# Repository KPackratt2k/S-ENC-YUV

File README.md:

# S-ENC-YUV
A YPbPr mod kit for the first generation SNES and Super Famicom consoles utilizing the BA6592F and S-ENC (a.k.a. BA6594F) video encoder chips.

**NOTICE:** This mod has been abandoned for a variety of reasons. Due to the video encoder's color difference pins outputting in the YIQ (for NTSC) or YUV (for PAL) colorspace, there are inaccurate colors when using this mod. In addition, I've experienced noise in the Luma channel on the console I've tested this with and have been unable to elimiate it entirely. If you're looking to use an SNES console on an SDTV or PVM with YPbPr inputs, I would recommend using an RGB SCART cable and an external RGB-to-YPbPr transcoder instead. If you choose to perform this mod to your console, understand its drawbacks and perform at your own risk.

**IMPORTANT:** This mod is compatible with early SNES and Super Famicom console revisions (serial number beginning with UN272 or less) only. Later SNES and Super Famicom consoles which utilize the S-RGB encoder lack the Pb and Pr outputs necessary for this mod, therefore this mod will not work on later consoles.

Compatible revisions:
- SHVC-CPU-01
- SNS-CPU-GPM-01
- SNS-CPU-GPM-02
- SNSP-CPU-01
- SNSP-CPU-02

The SNES outputs at a 15KHz 240p resolution, which most modern HDTVs will not accept over Component YPbPr (even if it can accept it over Composite). Please refer to [this webpage](https://www.hdretrovision.com/240p) for a list of TVs that have been tested as well as instructions on how to determine if your set can accept a 240p input in the event you can't find your TV in the compatibility list. If your TV cannot accept 240p over Component, then you must use a dedicated video scaler (e.g. RetroTink 2X, RetroTink 5X, OSSC, Framemeister, or GBS Control) to upscale the 240p signal. Users of CRT SDTVs, PVMs, or BVMs may disregard this message.

------------

## Introduction

As more gamers discover the benefits that RGB has to offer over the bog-standard Composite, they are often faced with the confusion surrounding the available options for taking advantage of this feature. The first instinct would be to head on over to eBay or Amazon and buy the cheapest SCART cables they can find, only to be disappointed by the audio buzzing and interference caused by cheap unshielded cables. Higher quality options like HD Retrovision Component cables or SCART cables from Insurrection Industries, Retro Access, or Retro Gaming Cables tend to fluctuate in stock as more people buy them. This mod enables early SNES or Super Famicom console revisions to output YPbPr Component Video using a cheap readily available 3.5mm TRRS to 3x RCA cable in conjunction with the standard Nintendo Composite AV cables for sound.

------------

## Variations

There are multiple variations of the mod board to choose from based on the two different methods tested. The one to choose will vary on a variety of factors (such as your video encoder chip, console revision, or even your TV/Scaler's way of processing the image). Type A uses a transistor setup similar to the original AV output circuit of the SNES and is best suited for the BA6592F encoder (common on most SHVC-CPU-01 consoles), while Type B uses basic passive components and is suited best for the S-ENC encoder (common on all other compatible revisions). If you're not sure which one to use, order the advanced full-size board and test it with different configurations to see which one works best for you.

OSHPark links:
- [Advanced](https://oshpark.com/shared_projects/vhEn3k7J)
- [Mini Type-A](https://oshpark.com/shared_projects/W2nKIRFb)
- [Mini Type-B](https://oshpark.com/shared_projects/YYqaIlj8)
- [Multi-Out Board for easy installation](https://oshpark.com/shared_projects/abuhMZIt)

It is recommended to order the small Multi-Out board with a 0.8 mm thickness.

-----------

## Output Cable

It is recommended to use an XBOX 360 E Composite AV cable (easy to find for cheap) in the following configuration:
- **Yellow**: Component Y
- **White**: Component Pb
- **Red**: Component Pr

When using the wiring configuration mentioned in the mod instructions, the cable will work as intended.

I've decided against using RCA jacks for this mod because the SHVC-CPU-01 revision does not have enough room to place them on the back panel as most of the space there is taken up by the sound module.

This cable will not provide audio. You must use your old Composite AV cables to provide the audio from the console.

-----------

## Board Assembly

Refer to the Bill of Materials (BOM) documents for each board depending on the one you'll be using. Populate the components accordingly to the correct locations and solder them into place. In addition to the parts listed in the corresponding BOM documents, you will need:
- Black, Red, Yellow, Green, and Blue colored wires (I recommend 28 AWG rainbow ribbon cable for this)
- Solid core wire or leads cut from a component
- Kapton tape or electrical tape
- Double-sided tape or adhesive pads
- A Game-bit screwdriver (for opening the console)
- A Philips screwdriver (for removing the screws that hold the motherboard in place)
- Heat shrink tubes
- Soldering iron
- Side cutters
- A drill with 2mm (5/16") and 6mm (1/4") drill bits
- Q-Tip (for cleaning any residing flux)
- Isopropyl alcohol (for cleaning any residing flux)

### Advanced Board Configurations

#### Type A:
- Leave R3, R4, RV1, and RV2 unpopulated.
- Jumper R3 and R4 with solid core wire or legs from a spare component.

#### Type B:
- Leave R1, R2, D1, D2, Q1, and Q2 unpopulated.
- Jumper the D1 anode pad to the Q1 emitter pad.
- Jumper the D2 anode pad to the Q2 emitter pad.

#### Type C (WIP):
- Assemble the board in the Type B configuration, wire the board to the console, test it, and adjust the pots until the image looks correct to you.
- After adjustments are made, measure the resistance on VR1 from the negative leg of C1 to the Pb output pad, and get the closest matching resistor. Make note of the resistance so you don't mistake one resistor for another.
- Measure VR2 resistance from the negative leg of C2 to the Pr output pad, and get the closest matching resistor. Make note of its resistance.
- Remove VR1 and VR2, and install the matching resistors for Pb into R3, and the resistor for Pr into R4.

------------

## Installation

WIP: Images to be added soon and instructions will improve gradually once I have the time to finish it.

Completely disassemble your SNES or Super Famicom console and inspect the video encoder chip to determine which configuration is suitable for your console. If yours is a BA6592F encoder, the Type-A configuration should provide the best results. If it's an S-ENC or a BA6594F, then the Type-B configuration should be sufficient.

Once you have decided which configuration to use based on your video encoder type, assemble the S-ENC mod board using the BOM (Bill of Materials) and the photos above as reference.

On the back of the console motherboard, solder the Multi-Out board onto the console's AV Multi-Out connector. Make sure you don't accidentally bridge any connections in the process. Use flux if you have any available. Gently remove residing flux with a Q-Tip and isopropyl alcohol when finished.

Solder the Yellow wire to the 5V pad (optional for Types B and C), the Green wire to the Y pad, and the Black wire to the GND pad.

Reinstall the bottom shield onto the SNES motherboard, and take care routing the wires from the Multi-Out board when doing so. Avoid routing the wires close to the screw posts as doing so may cause them to get pinched and short out as a result.

Turn the console motherboard onto the front, solder the red wire onto pin 1 of the video encoder chip (the bottom-left corner pin marked by the dot) and the blue wire onto pin 24 (the top-left corner pin). On some motherboard revisions, the numbers of the pins may be labeled, which makes it easier to tell where your wires need to go.

Reinstall the RF modulator shield onto place, reinsert the screws that hold it in place, and apply electrical or kapton tape on the side above the RF modulator/jack panel.

Apply Kapton tape onto the back of the mod board, then apply the double-sided tape/adhesive pad onto the same side.

Be sure to remove the backing on the double-sided tape once applied to the board.

Stick the mod board on top of the RF shield as close to the side facing the jack panel as possible, with the output pads facing left and the input pads facing right.

Place the wires onto the corresponding input pads and cut them to size so there's as little slack as possible.

**Color Guide:**
- Black: Ground
- Yellow: 5V (Not needed for Type B/C)
- Red: Pr
- Blue: Pb
- Green: Y

Once the wires are cut to size, strip them, then tin both the wire ends and the pads on the board. Solder the wires onto their corresponding pads.

Before drilling the hole for the 3.5mm jack, apply painter's tape on the right-side of the back of the shell, take the nut off the jack, place it on the bottom-right corner of the back of the shell (next to the power jack) with the outside of the nut on the edges of the corner, then use a pencil to draw the hole inside the nut on the tape. Once you have done this, use a ruler to draw lines in the middle of the hole to aid with drilling the pilot hole for the jack.

Use a small drill bit (5/16") to drill a hole on the right-side of the bottom shell where the 3.5mm jack will be mounted. Once the small hole is drilled, use an M7x0.75 (6mm or 1/4") drill bit to enlarge the hole. Take your time when drilling the holes and be careful not to drill too fast as the plastic can be brittle depending on how well the console has been taken care of during its lifetime. Test fit the jack and enlarge the hole slightly more if necessary.

Solder wires onto the jack on the following pins:
1. Green (Sleeve)
2. Blue (Tip)
3. Red (Ring 1)
4. Black (Ring 2)

Refer to the [SJ1-43502PM Datasheet](https://www.cuidevices.com/product/resource/sj1-43502pm.pdf) for pin locations.

Once you have the wires soldered onto the jack, it would be a good idea to add heat shrink tubes onto them to reduce stress on the wires and prevent any shorts.

Install the 3.5mm jack and the SNES motherboard in the bottom shell, run the wires from the jack onto the output pads on the mod board, cut the wires to size, strip the ends of the wires, tin both the mod board pads and the wires, and solder the wires onto the corresponding pads.

Once you have the board wired up, it may be a good idea to test the console to see if the mod works. If using the Type B configuration, adjust the potentiometers until the colors look correct.

If everything is working the way it should, you can reassemble the console and enjoy.

------------

## Credits

- Nicolas Livaditis
- thesteve
- Duo_R
- Michael Moffitt
- The Console5 Wiki
- The NESDev Forum
- The PC Engine-FX Forum

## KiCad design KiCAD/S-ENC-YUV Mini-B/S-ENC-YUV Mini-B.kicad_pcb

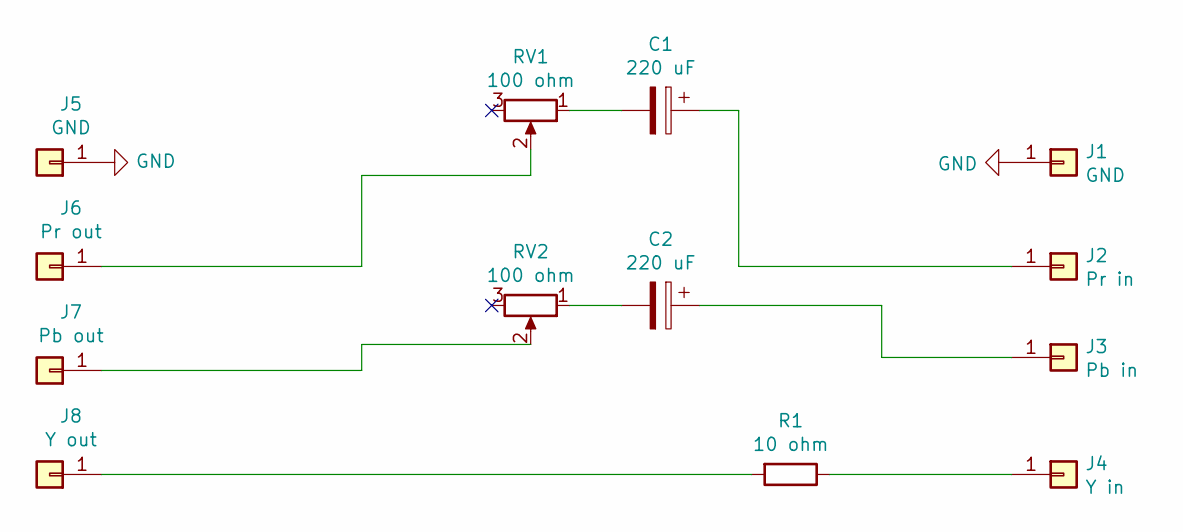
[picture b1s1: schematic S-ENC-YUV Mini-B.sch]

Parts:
C1, C2: 220 uF; CP_Radial_D6.3mm_P2.50mm
J1, J5: GND; SolderWirePad_1x01_SMD_5x10mm
J2: Pr in; SolderWirePad_1x01_SMD_5x10mm
J3: Pb in; SolderWirePad_1x01_SMD_5x10mm
J4: Y in; SolderWirePad_1x01_SMD_5x10mm
J6: Pr out; SolderWirePad_1x01_SMD_5x10mm
J7: Pb out; SolderWirePad_1x01_SMD_5x10mm
J8: Y out; SolderWirePad_1x01_SMD_5x10mm
R1: 10 ohm; R_Axial_DIN0207_L6.3mm_D2.5mm_P7.62mm_Horizontal
RV1, RV2: 100 ohm; Potentiometer_Bourns_3386P_Vertical

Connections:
GND: J1.1, J5.1
unnamed: C1.1, J2.1
unnamed: C1.2, RV1.1
unnamed: C2.1, J3.1
unnamed: C2.2, RV2.1
unnamed: J4.1, R1.1
unnamed: J6.1, RV1.2
unnamed: J7.1, RV2.2
unnamed: J8.1, R1.2

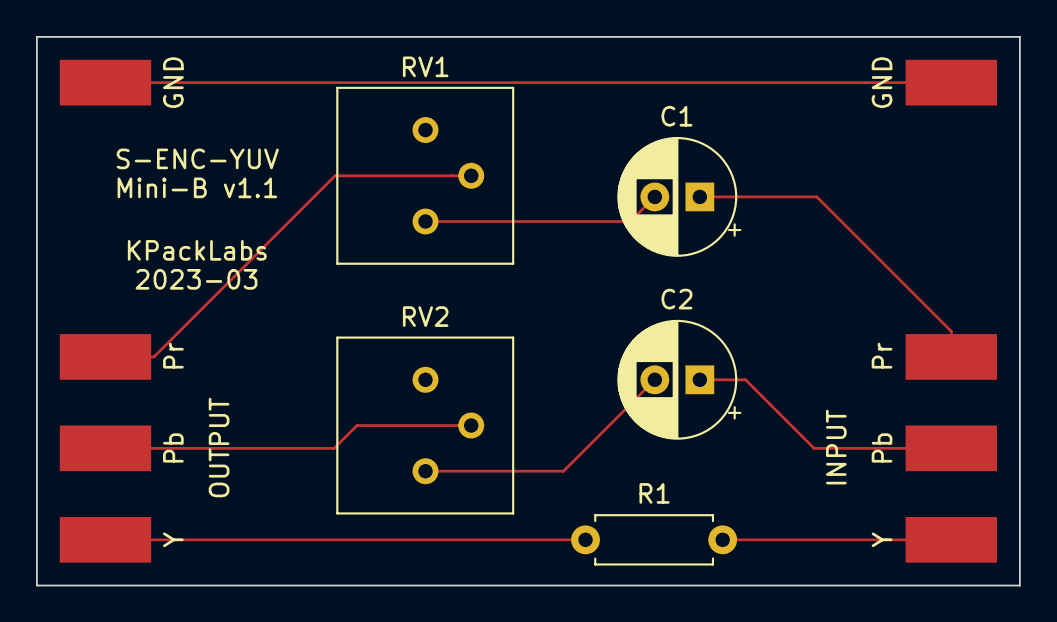
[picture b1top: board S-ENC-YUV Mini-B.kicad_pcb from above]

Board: 2 copper layers, 54.6 x 30.5 mm, 13 parts (0 on the bottom side), 9 nets.

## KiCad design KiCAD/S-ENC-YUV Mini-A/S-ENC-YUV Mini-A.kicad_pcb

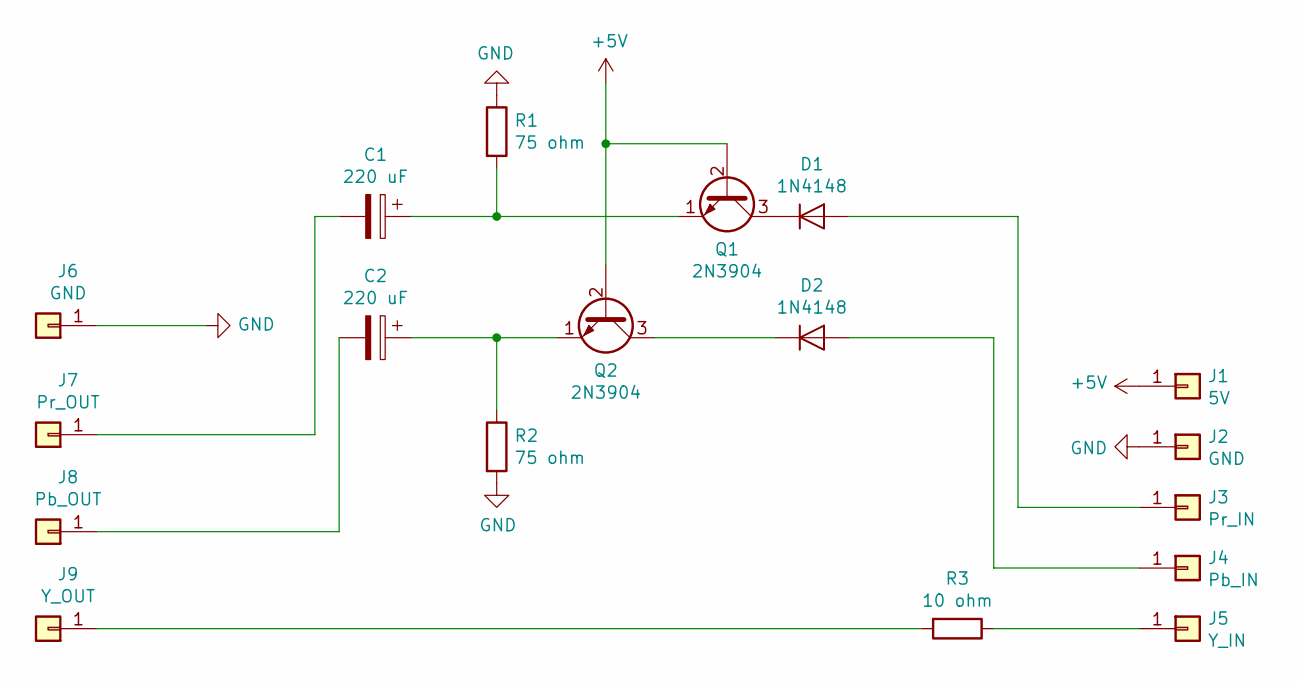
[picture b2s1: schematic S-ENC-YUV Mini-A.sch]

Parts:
C1, C2: 220 uF; CP_Radial_D6.3mm_P2.50mm
D1, D2: 1N4148; D_DO-35_SOD27_P7.62mm_Horizontal
J1: 5V; SolderWirePad_1x01_SMD_5x10mm
J2, J6: GND; SolderWirePad_1x01_SMD_5x10mm
J3: Pr_IN; SolderWirePad_1x01_SMD_5x10mm
J4: Pb_IN; SolderWirePad_1x01_SMD_5x10mm
J5: Y_IN; SolderWirePad_1x01_SMD_5x10mm
J7: Pr_OUT; SolderWirePad_1x01_SMD_5x10mm
J8: Pb_OUT; SolderWirePad_1x01_SMD_5x10mm
J9: Y_OUT; SolderWirePad_1x01_SMD_5x10mm
Q1, Q2: 2N3904; TO-92_Inline
R1, R2: 75 ohm; R_Axial_DIN0207_L6.3mm_D2.5mm_P7.62mm_Horizontal
R3: 10 ohm; R_Axial_DIN0207_L6.3mm_D2.5mm_P7.62mm_Horizontal

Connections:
+5V: J1.1, Q1.2 (B), Q2.2 (B)
GND: J2.1, J6.1, R1.1, R2.2
unnamed: C1.1, Q1.1 (E), R1.2
unnamed: C1.2, J7.1
unnamed: C2.1, Q2.1 (E), R2.1
unnamed: C2.2, J8.1
unnamed: D1.1 (K), Q1.3 (C)
unnamed: D1.2 (A), J3.1
unnamed: D2.1 (K), Q2.3 (C)
unnamed: D2.2 (A), J4.1
unnamed: J5.1, R3.1
unnamed: J9.1, R3.2

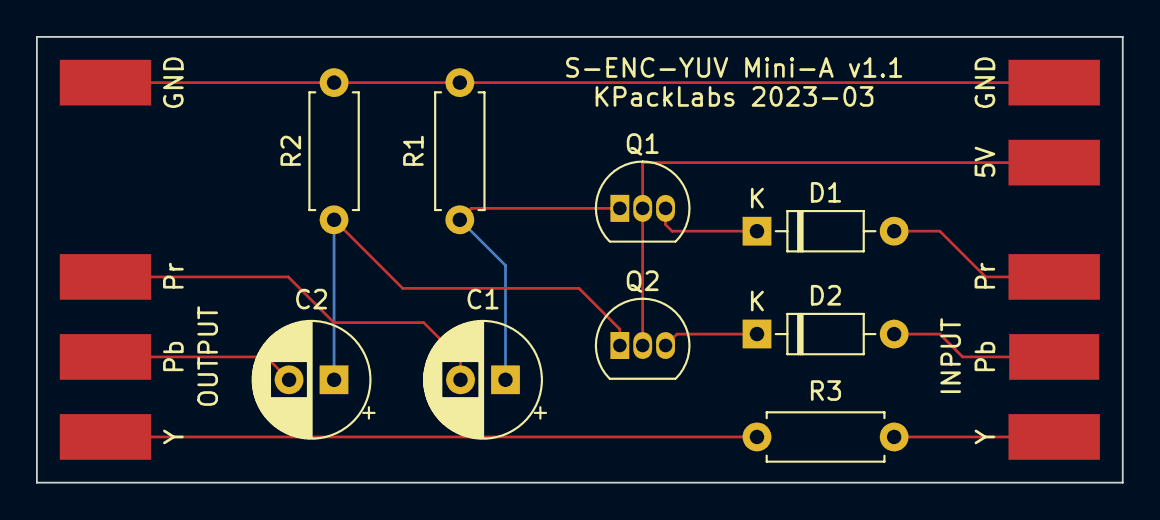
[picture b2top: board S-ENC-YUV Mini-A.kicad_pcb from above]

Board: 2 copper layers, 60.3 x 24.8 mm, 18 parts (0 on the bottom side), 12 nets.

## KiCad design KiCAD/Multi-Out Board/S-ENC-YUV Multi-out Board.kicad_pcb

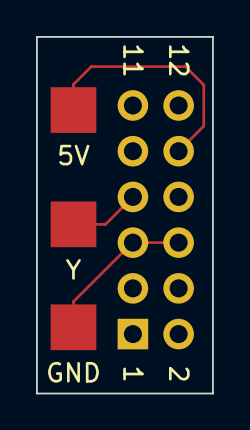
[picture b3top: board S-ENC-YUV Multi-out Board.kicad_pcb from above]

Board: 2 copper layers, 9.8 x 19.8 mm, 4 parts (1 on the bottom side), 3 nets.

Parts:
J1: SNES_Multiout; PinHeader_2x06_P2.54mm_Vertical
J2: 5V; SolderWirePad_1x01_SMD_5x10mm
J3: Y; SolderWirePad_1x01_SMD_5x10mm
J4: GND; SolderWirePad_1x01_SMD_5x10mm

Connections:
unnamed: J1.5, J1.6, J4.1
unnamed: J1.7, J3.1
unnamed: J1.10, J2.1

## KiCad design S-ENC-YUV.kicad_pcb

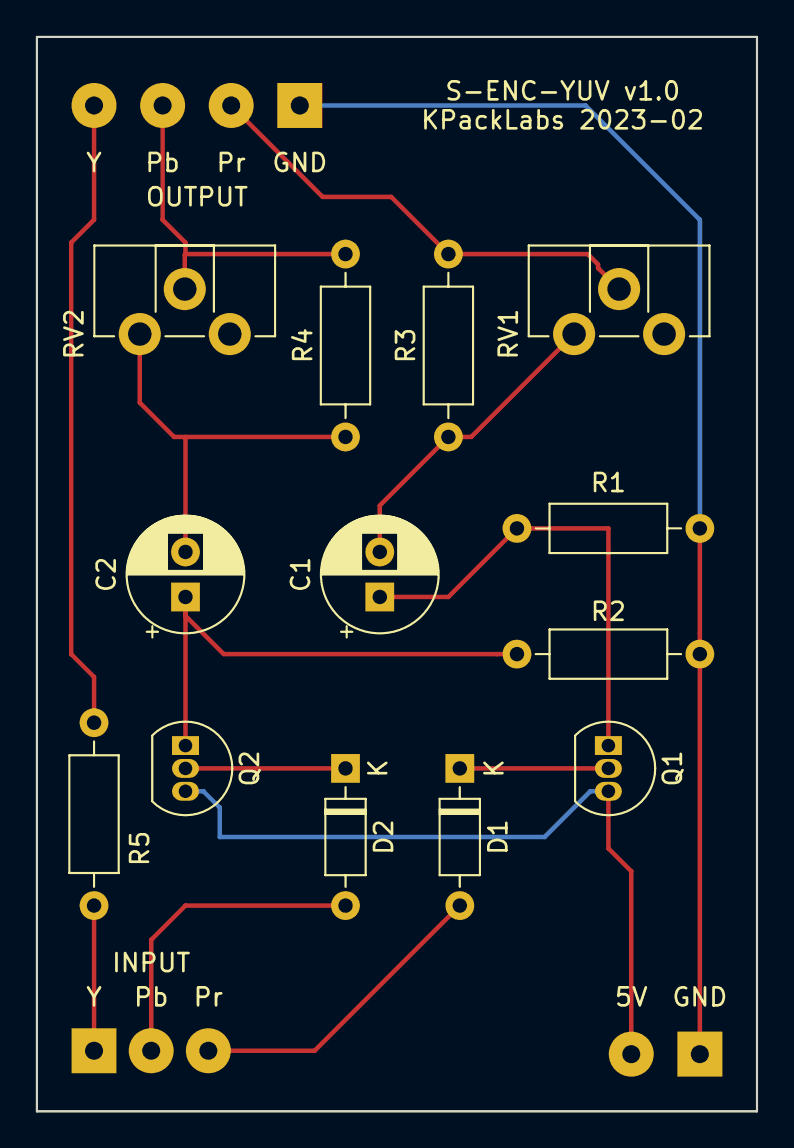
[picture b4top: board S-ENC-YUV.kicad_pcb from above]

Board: 2 copper layers, 40.0 x 59.7 mm, 16 parts (0 on the bottom side), 14 nets.

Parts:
C1, C2: 220 uF; CP_Radial_D6.3mm_P2.50mm
D1, D2: 1n4148; D_DO-35_SOD27_P7.62mm_Horizontal
J1: Conn_01x02; SolderWirePad_1x02_P3.81mm_Drill1mm
J2: Conn_01x03; SolderWirePad_1x03_P3.175mm_Drill1mm
J3: Conn_01x04; SolderWirePad_1x04_P3.81mm_Drill1mm
Q1, Q2: S8050; TO-92_Inline
R1, R2: 75 ohm; R_Axial_DIN0207_L6.3mm_D2.5mm_P10.16mm_Horizontal
R3, R4: 0-100 ohm; R_Axial_DIN0207_L6.3mm_D2.5mm_P10.16mm_Horizontal
R5: 10 ohm; R_Axial_DIN0207_L6.3mm_D2.5mm_P10.16mm_Horizontal
RV1, RV2: 0-100 ohm; Potentiometer_ACP_CA9-H2,5_Horizontal

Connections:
/+5V: J1.2, Q1.3, Q2.3
GND: J1.1, J3.1, R1.1, R2.2
unnamed: C1.1, Q1.1, R1.2
unnamed: C1.2, R3.1, RV1.1
unnamed: C2.1, Q2.1, R2.1
unnamed: C2.2, R4.1, RV2.1
unnamed: D1.1, Q1.2
unnamed: D1.2, J2.3
unnamed: D2.1, Q2.2
unnamed: D2.2, J2.2
unnamed: J2.1, R5.1
unnamed: J3.2, R3.2, RV1.2
unnamed: J3.3, R4.2, RV2.2
unnamed: J3.4, R5.2

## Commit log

2023-02-20 Add directory
2023-02-20 Move to directory
2023-02-20 Inital commit
2023-02-20 Update Readme
    Added complete information on the mod.
2023-02-20 Fixed board link formatting
2023-02-20 Fixed credits
2023-02-24 Updated the readme
2023-02-24 Updated the readme again
    Clarified which video encoders are best suited for certain configurations and added Imperial drill bit sizes.
2023-03-12 Updated the readme to correct some information
2023-03-18 Added images in their own folder
2023-03-18 Update README.md
    Added some images.
2023-03-24 Updated Mini-A PCB
    Fixed text rotation on the Output side.
2023-03-24 Updated Mini-B PCB
    Fixed text rotation on the Output side.
2023-03-24 Updated OSHPark links to Mini boards
